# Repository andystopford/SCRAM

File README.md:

# SCRAM
Auto-shutdown for LaPavoni P67 espresso machine.

SCRAM is a backronym for Safety Control Relay Actuator Mechanism (clumsy, but irresistable)

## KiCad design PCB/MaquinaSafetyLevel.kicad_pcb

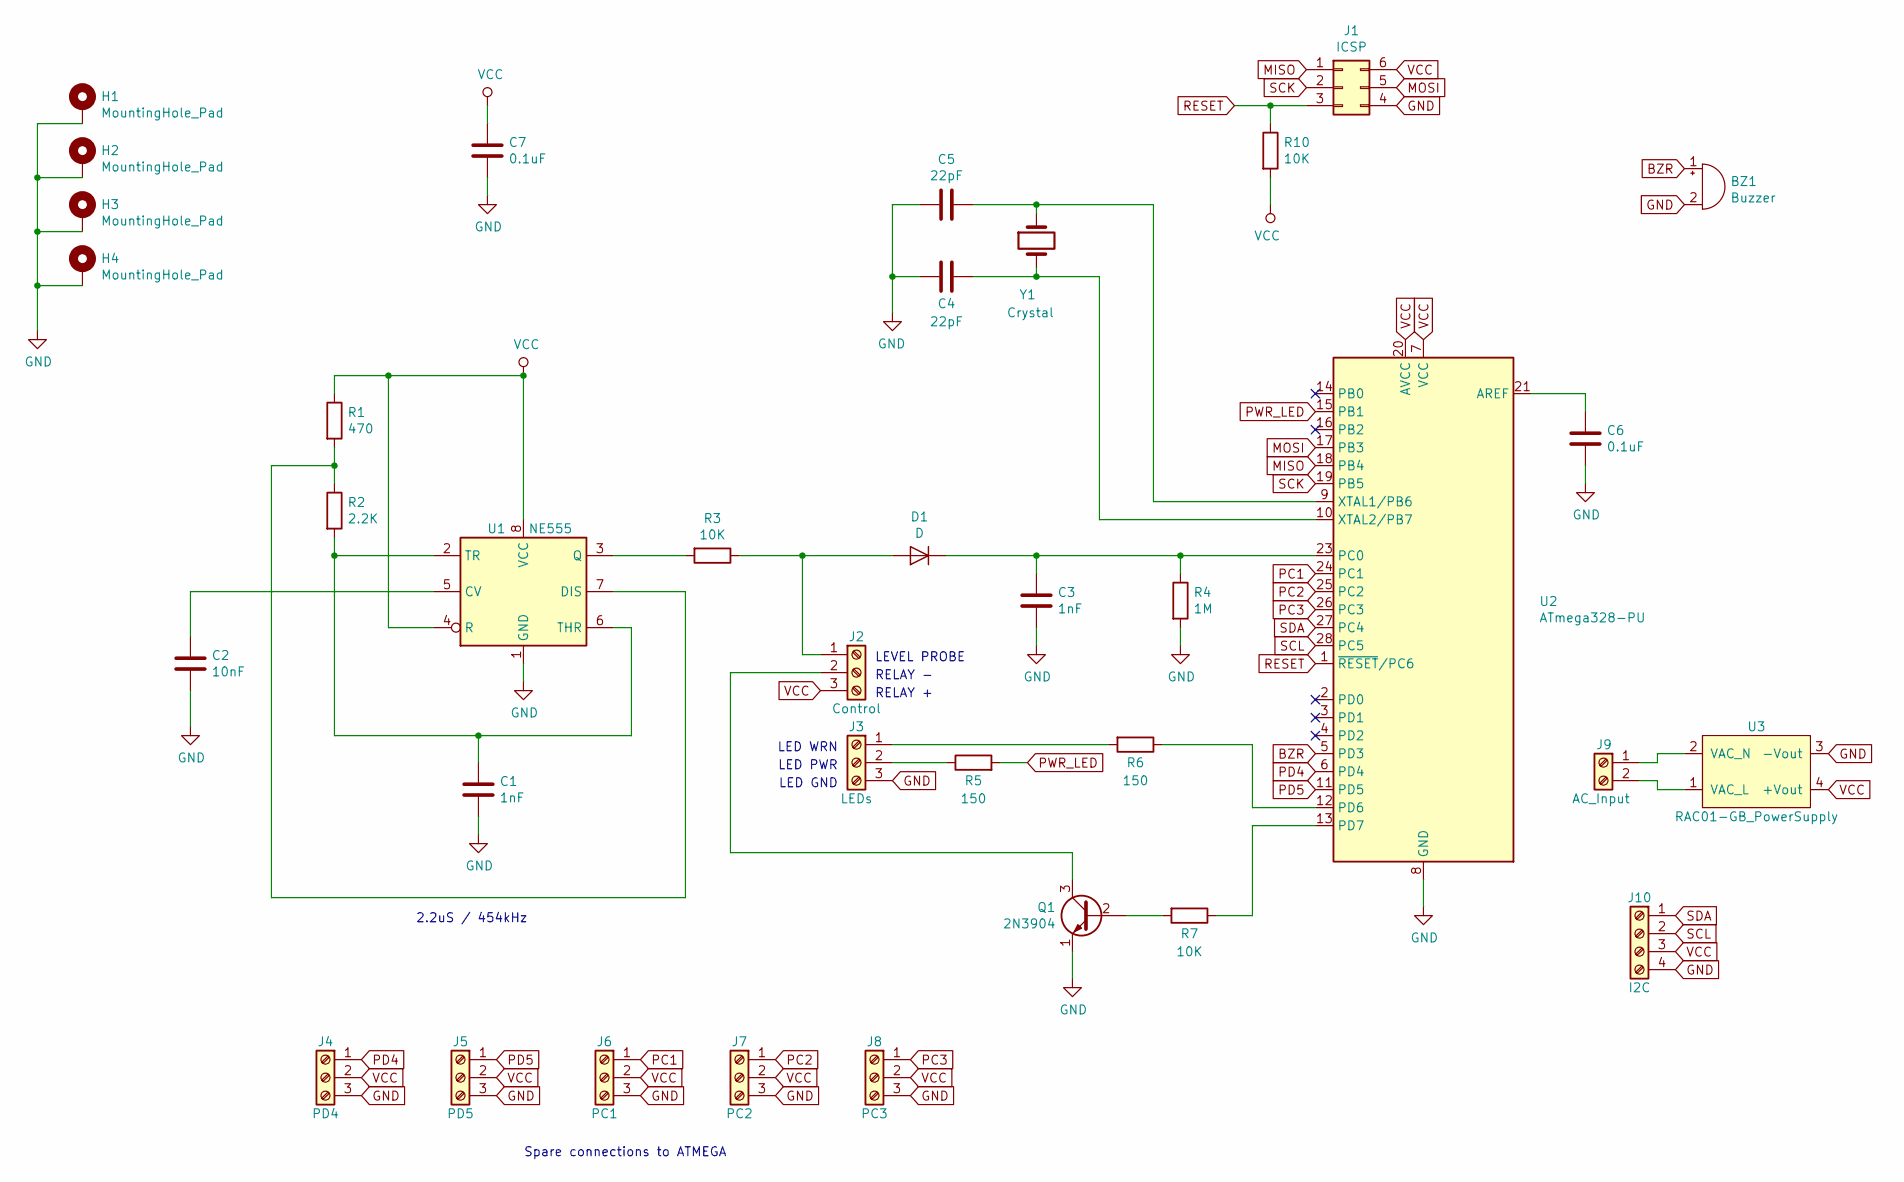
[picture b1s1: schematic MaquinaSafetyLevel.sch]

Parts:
BZ1: Buzzer; Buzzer_10.16pitch
C1, C3: 1nF; C_Disc_D5.0mm_W2.5mm_P5.00mm
C2: 10nF; C_Disc_D5.0mm_W2.5mm_P5.00mm
C4, C5: 22pF; C_Disc_D8.0mm_W5.0mm_P10.00mm
C6, C7: 0.1uF; C_Rect_L18.0mm_W5.0mm_P15.00mm_FKS3_FKP3
D1: D; D_A-405_P7.62mm_Horizontal
H1, H2, H3, H4: MountingHole_Pad; MountingHole_4.3mm_M4_ISO7380_Pad
J1: ICSP; PinHeader_2x03_P2.54mm_Vertical
J2: Control; MB312-254_TerminalBlock_3Way
J3: LEDs; MB312-254_TerminalBlock_3Way
J4: PD4; MB312-254_TerminalBlock_3Way
J5: PD5; MB312-254_TerminalBlock_3Way
J6: PC1; MB312-254_TerminalBlock_3Way
J7: PC2; MB312-254_TerminalBlock_3Way
J8: PC3; MB312-254_TerminalBlock_3Way
J9: AC_Input; 5.08_PCB_2Way
J10: I2C; MB312-254_TerminalBlock_4Way
Q1: 2N3904; TO-92_HandSolder
R1: 470; R_Axial_DIN0207_L6.3mm_D2.5mm_P7.62mm_Horizontal
R2: 2.2K; R_Axial_DIN0207_L6.3mm_D2.5mm_P10.16mm_Horizontal
R3, R7, R10: 10K; R_Axial_DIN0207_L6.3mm_D2.5mm_P10.16mm_Horizontal
R4: 1M; R_Axial_DIN0207_L6.3mm_D2.5mm_P10.16mm_Horizontal
R5, R6: 150; R_Axial_DIN0207_L6.3mm_D2.5mm_P10.16mm_Horizontal
U1: NE555; DIP-8_W7.62mm
U2: ATmega328-PU; DIP-28_W7.62mm
U3: RAC01-GB_PowerSupply
Y1: Crystal; Crystal_HC49-4H_Vertical

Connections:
BZR: BZ1.1 (-), U2.5 (PD3)
GND: BZ1.2 (+), C1.2, C2.2, C3.2, C4.1, C5.1, C6.2, C7.2, H1.1, H2.1, H3.1, H4.1, J1.4, J3.3, J4.3, J5.3, J6.3, J7.3, J8.3, J10.4, Q1.1 (E), R4.2, U1.1 (GND), U2.8 (GND), U2.22 (GND), U3.3 (-Vout)
MISO: J1.1, U2.18 (PB4)
MOSI: J1.5, U2.17 (PB3)
unnamed: C1.1, R2.2, U1.2 (TR), U1.6 (THR)
unnamed: C2.1, U1.5 (CV)
unnamed: C3.1, D1.1 (K), R4.1, U2.23 (PC0)
unnamed: C4.2, U2.10 (XTAL2/PB7), Y1.2
unnamed: C5.2, U2.9 (XTAL1/PB6), Y1.1
unnamed: C6.1, U2.21 (AREF)
unnamed: D1.2 (A), J2.1, R3.1
unnamed: J2.2, Q1.3 (C)
unnamed: J3.1, R6.2
unnamed: J3.2, R5.1
unnamed: J9.1, U3.2 (VAC_N)
unnamed: J9.2, U3.1 (VAC_L)
unnamed: Q1.2 (B), R7.2
unnamed: R1.2, R2.1, U1.7 (DIS)
unnamed: R3.2, U1.3 (Q)
unnamed: R6.1, U2.12 (PD6)
unnamed: R7.1, U2.13 (PD7)
PC1: J6.1, U2.24 (PC1)
PC2: J7.1, U2.25 (PC2)
PC3: J8.1, U2.26 (PC3)
PD4: J4.1, U2.6 (PD4)
PD5: J5.1, U2.11 (PD5)
PWR_LED: R5.2, U2.15 (PB1)
RESET: J1.3, R10.1, U2.1 (~RESET~/PC6)
SCK: J1.2, U2.19 (PB5)
SCL: J10.2, U2.28 (PC5)
SDA: J10.1, U2.27 (PC4)
VCC: C7.1, J1.6, J2.3, J4.2, J5.2, J6.2, J7.2, J8.2, J10.3, R1.1, R10.2, U1.4 (R), U1.8 (VCC), U2.7 (VCC), U2.20 (AVCC), U3.4 (+Vout)

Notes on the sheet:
2.2uS / 454kHz
LED PWR
LED WRN
RELAY -
LEVEL PROBE
Spare connections to ATMEGA
RELAY +
LED GND

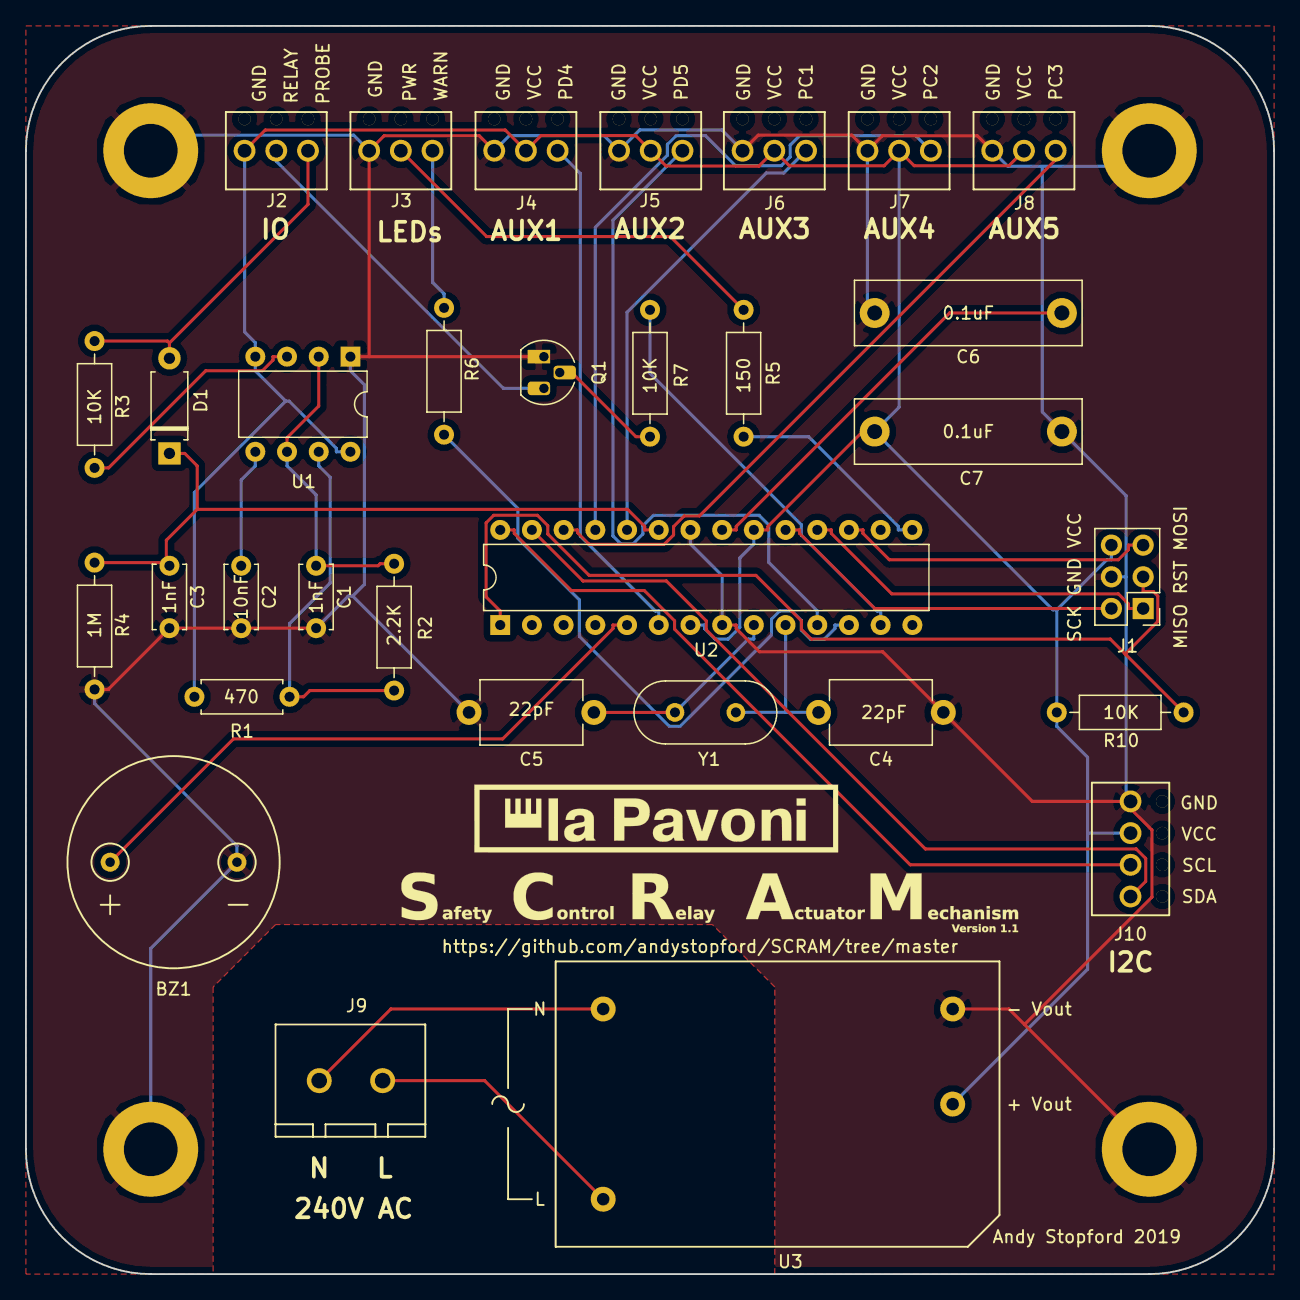
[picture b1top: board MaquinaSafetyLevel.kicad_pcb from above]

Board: 2 copper layers, 100.0 x 100.0 mm, 38 parts (0 on the bottom side), 32 nets.

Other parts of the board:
G1: LOGO; name
G2: LOGO; logo

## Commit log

2019-09-29 Initial git commit
2019-09-29 V1.1 PCB, as ordered.
2019-09-29 Removed folder from repository
2019-10-17 Code tested and working
2020-08-07 Photos added
